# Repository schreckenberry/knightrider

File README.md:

# knightrider

project for university, blinking some ws2812b with a stm32f4/7

...git just because, nothing spectecular

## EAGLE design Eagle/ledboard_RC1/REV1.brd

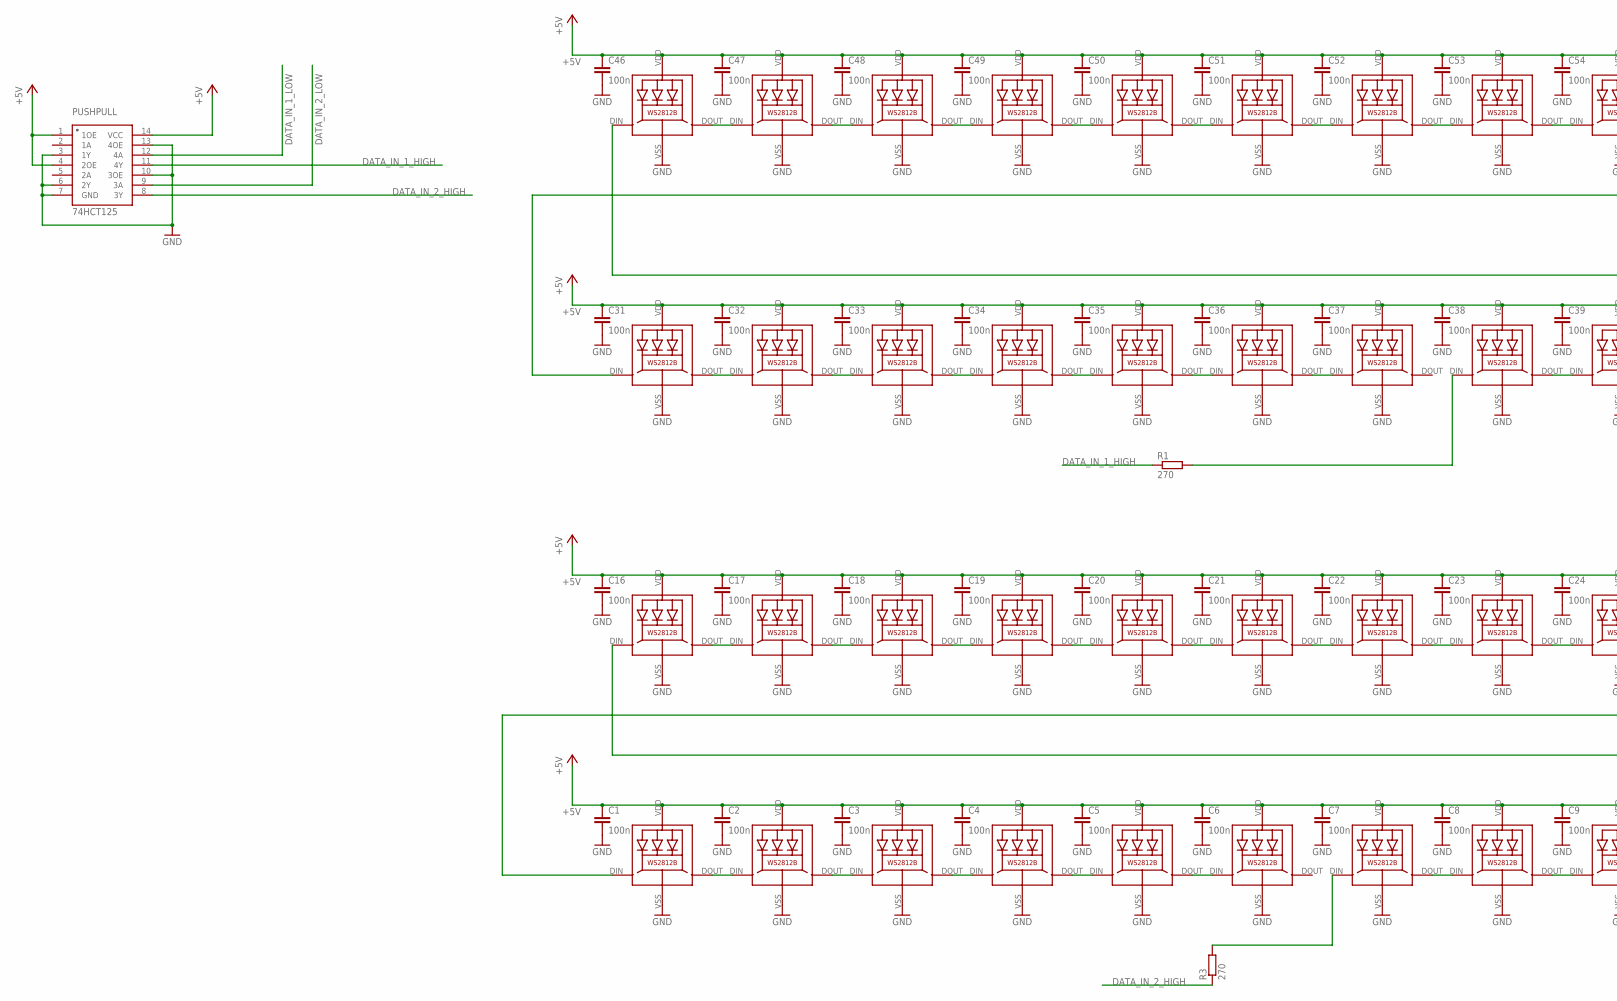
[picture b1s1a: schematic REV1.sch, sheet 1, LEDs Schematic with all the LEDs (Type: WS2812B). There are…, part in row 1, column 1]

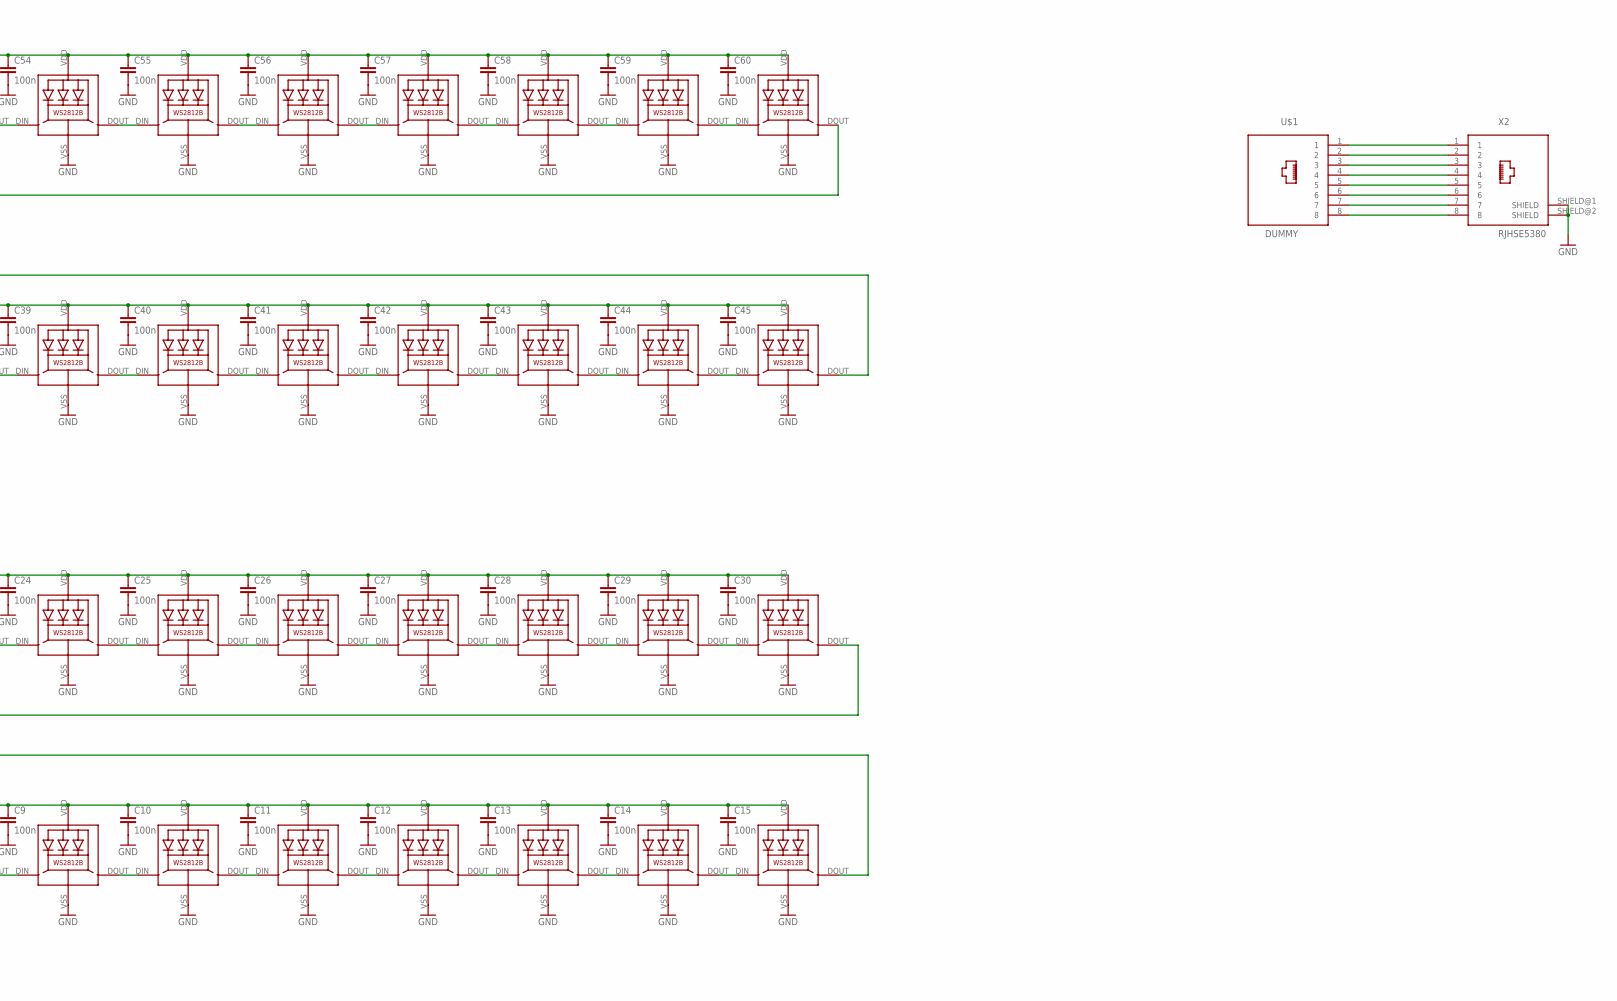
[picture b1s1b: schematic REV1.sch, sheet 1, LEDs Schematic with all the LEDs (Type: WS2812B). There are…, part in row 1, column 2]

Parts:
C1, C2, C3, C4, C5, C6, C7, C8, C9, C10, C11, C12, C13, C14, C15, C16, C17, C18, C19, C20, C21, C22, C23, C24, C25, C26, C27, C28, C29, C30, C31, C32, C33, C34, C35, C36, C37, C38, C39, C40, C41, C42, C43, C44, C45, C46, C47, C48, C49, C50, C51, C52, C53, C54, C55, C56, C57, C58, C59, C60: 100n; C0603
LED1, LED2, LED3, LED4, LED5, LED6, LED7, LED8, LED9, LED10, LED11, LED12, LED13, LED14, LED15, LED16, LED17, LED18, LED19, LED20, LED21, LED22, LED23, LED24, LED25, LED26, LED27, LED28, LED29, LED30, LED31, LED32, LED33, LED34, LED35, LED36, LED37, LED38, LED39, LED40, LED41, LED42, LED43, LED44, LED45, LED46, LED47, LED48, LED49, LED50, LED51, LED52, LED53, LED54, LED55, LED56, LED57, LED58, LED59, LED60: WS2812B
PUSHPULL: 74HCT125; SO-14DW
R1, R3: 270; R0603
U$1: DUMMY
X2: RJHSE5380

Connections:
+5V: C1.1, C2.1, C3.1, C4.1, C5.1, C6.1, C7.1, C8.1, C9.1, C10.1, C11.1, C12.1, C13.1, C14.1, C15.1, C16.1, C17.1, C18.1, C19.1, C20.1, C21.1, C22.1, C23.1, C24.1, C25.1, C26.1, C27.1, C28.1, C29.1, C30.1, C31.1, C32.1, C33.1, C34.1, C35.1, C36.1, C37.1, C38.1, C39.1, C40.1, C41.1, C42.1, C43.1, C44.1, C45.1, C46.1, C47.1, C48.1, C49.1, C50.1, C51.1, C52.1, C53.1, C54.1, C55.1, C56.1, C57.1, C58.1, C59.1, C60.1, LED1.VDD, LED2.VDD, LED3.VDD, LED4.VDD, LED5.VDD, LED6.VDD, LED7.VDD, LED8.VDD, LED9.VDD, LED10.VDD, LED11.VDD, LED12.VDD, LED13.VDD, LED14.VDD, LED15.VDD, LED16.VDD, LED17.VDD, LED18.VDD, LED19.VDD, LED20.VDD, LED21.VDD, LED22.VDD, LED23.VDD, LED24.VDD, LED25.VDD, LED26.VDD, LED27.VDD, LED28.VDD, LED29.VDD, LED30.VDD, LED31.VDD, LED32.VDD, LED33.VDD, LED34.VDD, LED35.VDD, LED36.VDD, LED37.VDD, LED38.VDD, LED39.VDD, LED40.VDD, LED41.VDD, LED42.VDD, LED43.VDD, LED44.VDD, LED45.VDD, LED46.VDD, LED47.VDD, LED48.VDD, LED49.VDD, LED50.VDD, LED51.VDD, LED52.VDD, LED53.VDD, LED54.VDD, LED55.VDD, LED56.VDD, LED57.VDD, LED58.VDD, LED59.VDD, LED60.VDD, PUSHPULL.1 (1OE), PUSHPULL.4 (2OE), PUSHPULL.14 (VCC); also elsewhere on the board
DATA_IN_1_HIGH: PUSHPULL.11 (4Y), R1.1
DATA_IN_1_LOW: PUSHPULL.12 (4A); also elsewhere on the board
DATA_IN_2_HIGH: PUSHPULL.8 (3Y), R3.1
DATA_IN_2_LOW: PUSHPULL.9 (3A); also elsewhere on the board
GND: C1.2, C2.2, C3.2, C4.2, C5.2, C6.2, C7.2, C8.2, C9.2, C10.2, C11.2, C12.2, C13.2, C14.2, C15.2, C16.2, C17.2, C18.2, C19.2, C20.2, C21.2, C22.2, C23.2, C24.2, C25.2, C26.2, C27.2, C28.2, C29.2, C30.2, C31.2, C32.2, C33.2, C34.2, C35.2, C36.2, C37.2, C38.2, C39.2, C40.2, C41.2, C42.2, C43.2, C44.2, C45.2, C46.2, C47.2, C48.2, C49.2, C50.2, C51.2, C52.2, C53.2, C54.2, C55.2, C56.2, C57.2, C58.2, C59.2, C60.2, LED1.VSS (GND), LED2.VSS (GND), LED3.VSS (GND), LED4.VSS (GND), LED5.VSS (GND), LED6.VSS (GND), LED7.VSS (GND), LED8.VSS (GND), LED9.VSS (GND), LED10.VSS (GND), LED11.VSS (GND), LED12.VSS (GND), LED13.VSS (GND), LED14.VSS (GND), LED15.VSS (GND), LED16.VSS (GND), LED17.VSS (GND), LED18.VSS (GND), LED19.VSS (GND), LED20.VSS (GND), LED21.VSS (GND), LED22.VSS (GND), LED23.VSS (GND), LED24.VSS (GND), LED25.VSS (GND), LED26.VSS (GND), LED27.VSS (GND), LED28.VSS (GND), LED29.VSS (GND), LED30.VSS (GND), LED31.VSS (GND), LED32.VSS (GND), LED33.VSS (GND), LED34.VSS (GND), LED35.VSS (GND), LED36.VSS (GND), LED37.VSS (GND), LED38.VSS (GND), LED39.VSS (GND), LED40.VSS (GND), LED41.VSS (GND), LED42.VSS (GND), LED43.VSS (GND), LED44.VSS (GND), LED45.VSS (GND), LED46.VSS (GND), LED47.VSS (GND), LED48.VSS (GND), LED49.VSS (GND), LED50.VSS (GND), LED51.VSS (GND), LED52.VSS (GND), LED53.VSS (GND), LED54.VSS (GND), LED55.VSS (GND), LED56.VSS (GND), LED57.VSS (GND), LED58.VSS (GND), LED59.VSS (GND), LED60.VSS (GND), PUSHPULL.3 (1Y), PUSHPULL.6 (2Y), PUSHPULL.7 (GND), PUSHPULL.10 (3OE), PUSHPULL.13 (4OE), X2.SHIELD@1 (SHIELD), X2.SHIELD@2 (SHIELD); also elsewhere on the board
unnamed: LED45.DOUT (DO), LED46.DIN (DI)
unnamed: LED46.DOUT (DO), LED47.DIN (DI)
unnamed: LED47.DOUT (DO), LED48.DIN (DI)
unnamed: LED48.DOUT (DO), LED49.DIN (DI)
unnamed: LED49.DOUT (DO), LED50.DIN (DI)
unnamed: LED50.DOUT (DO), LED51.DIN (DI)
unnamed: LED51.DOUT (DO), LED52.DIN (DI)
unnamed: LED52.DOUT (DO), LED53.DIN (DI)
unnamed: LED53.DOUT (DO), LED54.DIN (DI)
unnamed: LED54.DOUT (DO), LED55.DIN (DI)
unnamed: LED55.DOUT (DO), LED56.DIN (DI)
unnamed: LED56.DOUT (DO), LED57.DIN (DI)
unnamed: LED57.DOUT (DO), LED58.DIN (DI)
unnamed: LED58.DOUT (DO), LED59.DIN (DI)
unnamed: LED59.DOUT (DO), LED60.DIN (DI)
unnamed: LED31.DIN (DI), LED60.DOUT (DO)
unnamed: LED1.DIN (DI), LED30.DOUT (DO)
unnamed: LED1.DOUT (DO), LED2.DIN (DI)
unnamed: LED2.DOUT (DO), LED3.DIN (DI)
unnamed: LED3.DOUT (DO), LED4.DIN (DI)
unnamed: LED4.DOUT (DO), LED5.DIN (DI)
unnamed: LED7.DIN (DI), R3.2
unnamed: LED5.DOUT (DO), LED6.DIN (DI)
unnamed: LED7.DOUT (DO), LED8.DIN (DI)
unnamed: LED8.DOUT (DO), LED9.DIN (DI)
unnamed: LED9.DOUT (DO), LED10.DIN (DI)
unnamed: LED10.DOUT (DO), LED11.DIN (DI)
unnamed: LED11.DOUT (DO), LED12.DIN (DI)
unnamed: LED12.DOUT (DO), LED13.DIN (DI)
unnamed: LED13.DOUT (DO), LED14.DIN (DI)
unnamed: LED14.DOUT (DO), LED15.DIN (DI)
unnamed: LED15.DOUT (DO), LED16.DIN (DI)
unnamed: LED16.DOUT (DO), LED17.DIN (DI)
unnamed: LED17.DOUT (DO), LED18.DIN (DI)
unnamed: LED18.DOUT (DO), LED19.DIN (DI)
unnamed: LED19.DOUT (DO), LED20.DIN (DI)
unnamed: LED20.DOUT (DO), LED21.DIN (DI)
unnamed: LED21.DOUT (DO), LED22.DIN (DI)
unnamed: LED22.DOUT (DO), LED23.DIN (DI)
unnamed: LED23.DOUT (DO), LED24.DIN (DI)
unnamed: LED24.DOUT (DO), LED25.DIN (DI)
unnamed: LED25.DOUT (DO), LED26.DIN (DI)
unnamed: LED26.DOUT (DO), LED27.DIN (DI)
unnamed: LED27.DOUT (DO), LED28.DIN (DI)
unnamed: LED28.DOUT (DO), LED29.DIN (DI)
unnamed: LED29.DOUT (DO), LED30.DIN (DI)
unnamed: LED38.DIN (DI), R1.2
unnamed: LED31.DOUT (DO), LED32.DIN (DI)
unnamed: LED32.DOUT (DO), LED33.DIN (DI)
unnamed: LED33.DOUT (DO), LED34.DIN (DI)
unnamed: LED34.DOUT (DO), LED35.DIN (DI)
unnamed: LED35.DOUT (DO), LED36.DIN (DI)
unnamed: LED36.DOUT (DO), LED37.DIN (DI)
unnamed: U$1.1, X2.1
unnamed: LED38.DOUT (DO), LED39.DIN (DI)
unnamed: LED39.DOUT (DO), LED40.DIN (DI)
unnamed: LED40.DOUT (DO), LED41.DIN (DI)
unnamed: LED41.DOUT (DO), LED42.DIN (DI)
unnamed: LED42.DOUT (DO), LED43.DIN (DI)
unnamed: LED43.DOUT (DO), LED44.DIN (DI)
unnamed: LED44.DOUT (DO), LED45.DIN (DI)
unnamed: U$1.2, X2.2
unnamed: U$1.3, X2.3
unnamed: U$1.4, X2.4
unnamed: U$1.5, X2.5
unnamed: U$1.6, X2.6
unnamed: U$1.7, X2.7
unnamed: U$1.8, X2.8

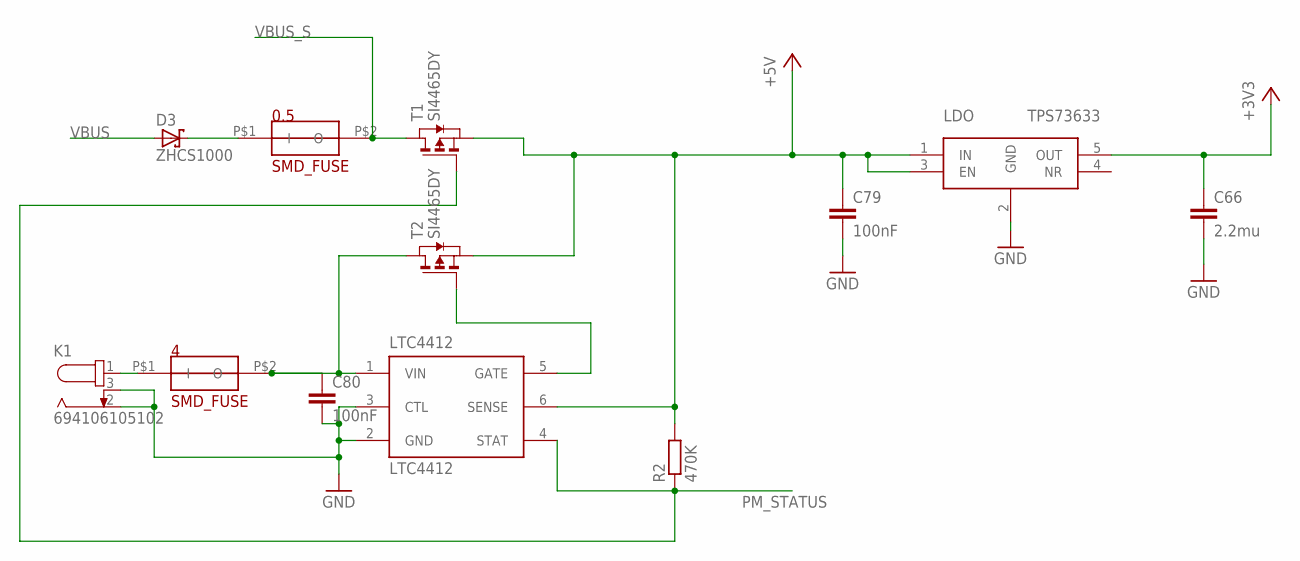
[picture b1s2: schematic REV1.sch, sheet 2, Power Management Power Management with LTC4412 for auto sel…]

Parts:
0.5, 4: SMD_FUSE; FUSE
C66: 2.2mu; C0603
C79, C80: 100nF; C0603
D3: ZHCS1000; SOT23
K1: 694106105102
LDO: TPS73633; SOT23-DBV
LTC4412: LTC4412; SOT23-6L
R2: 470K; R0603
T1, T2: SI4465DY; SO08

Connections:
+3V3: C66.1, LDO.5 (OUT); also elsewhere on the board
+5V: C79.1, LDO.1 (IN), LDO.3 (EN), LTC4412.6 (SENSE), R2.2, T1.1 (S), T1.2 (S), T1.3 (S), T2.1 (S), T2.2 (S), T2.3 (S); also elsewhere on the board
GND: C66.2, C79.2, C80.2, K1.2, K1.3, LDO.2 (GND), LTC4412.2 (GND), LTC4412.3 (CTL); also elsewhere on the board
unnamed: LTC4412.5 (GATE), T2.4 (G)
unnamed: 0.5.P$1 (I), D3.1 (C)
PM_STATUS: LTC4412.4 (STAT), R2.1, T1.4 (G); also elsewhere on the board
VBUS: D3.3 (A); also elsewhere on the board
VBUS_S: 0.5.P$2 (O), T1.5 (D), T1.6 (D), T1.7 (D), T1.8 (D); also elsewhere on the board
V_5: 4.P$2 (O), C80.1, LTC4412.1 (VIN), T2.5 (D), T2.6 (D), T2.7 (D), T2.8 (D)
V_IN: 4.P$1 (I), K1.1

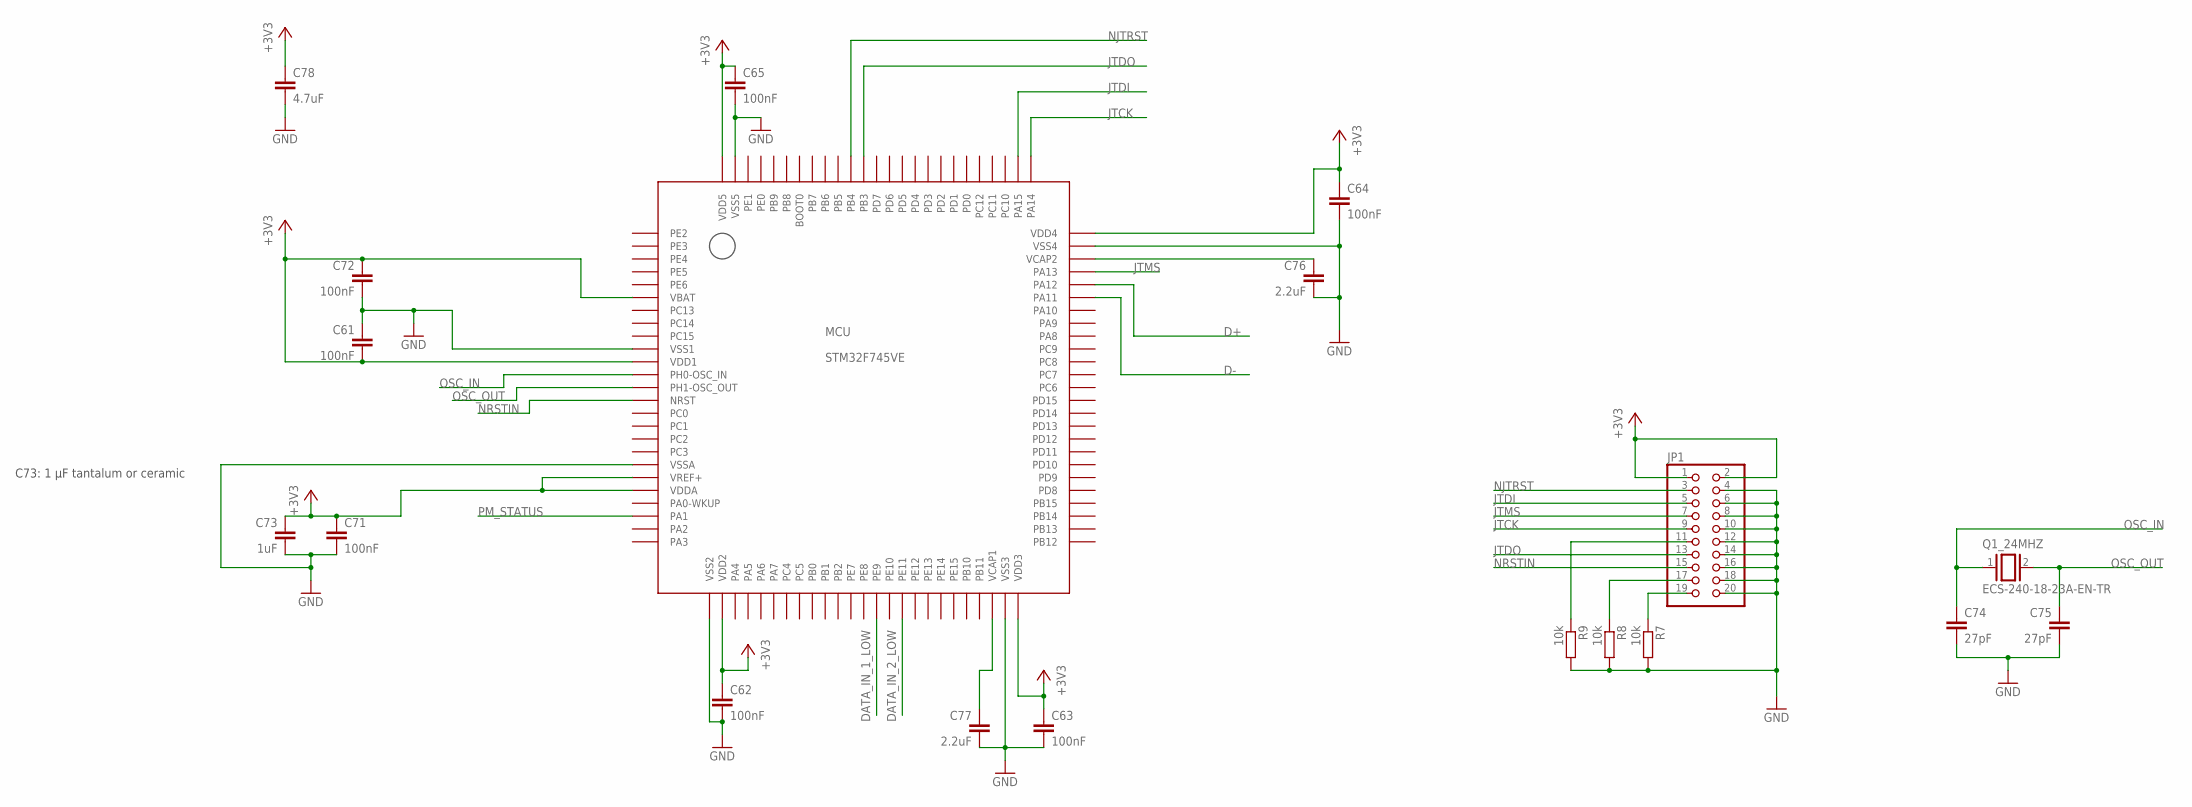
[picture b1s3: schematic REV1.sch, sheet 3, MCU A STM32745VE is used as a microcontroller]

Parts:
C61, C62, C63, C64, C65, C71, C72: 100nF; C0603
C73: 1uF; C0603
C74, C75: 27pF; C0603
C76, C77: 2.2uF; C0603
C78: 4.7uF; C0603
JP1: PINHD-2X10_2.54-SMD; 2X10SMD
MCU: STM32F745VE; LQFP100
Q1_24MHZ: ECS-240-18-23A-EN-TR; ESC64A
R7, R8, R9: 10k; R0603

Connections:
+3V3: C61.2, C62.1, C63.1, C64.1, C65.1, C71.1, C72.1, C73.1, C78.1, JP1.1, JP1.2, MCU.6 (VBAT), MCU.11 (VDD1), MCU.20 (VREF+), MCU.21 (VDDA), MCU.27 (VDD2), MCU.50 (VDD3), MCU.75 (VDD4), MCU.100 (VDD5); also elsewhere on the board
D+: MCU.71 (PA12); also elsewhere on the board
D-: MCU.70 (PA11); also elsewhere on the board
DATA_IN_1_LOW: MCU.39 (PE9); also elsewhere on the board
DATA_IN_2_LOW: MCU.41 (PE11); also elsewhere on the board
GND: C61.1, C62.2, C63.2, C64.2, C65.2, C71.2, C72.2, C73.2, C74.2, C75.2, C76.2, C77.2, C78.2, JP1.4, JP1.6, JP1.8, JP1.10, JP1.12, JP1.14, JP1.16, JP1.18, JP1.20, MCU.10 (VSS1), MCU.19 (VSSA), MCU.26 (VSS2), MCU.49 (VSS3), MCU.74 (VSS4), MCU.99 (VSS5), R7.2, R8.2, R9.2; also elsewhere on the board
JTCK: JP1.9, MCU.76 (PA14)
JTDI: JP1.5, MCU.77 (PA15)
JTDO: JP1.13, MCU.89 (PB3)
JTMS: JP1.7, MCU.72 (PA13)
unnamed: C77.1, MCU.48 (VCAP1)
unnamed: C76.1, MCU.73 (VCAP2)
unnamed: JP1.19, R7.1
unnamed: JP1.17, R8.1
unnamed: JP1.11, R9.1
NJTRST: JP1.3, MCU.90 (PB4)
NRSTIN: JP1.15, MCU.14 (NRST)
OSC_IN: C74.1, MCU.12 (PH0-OSC_IN), Q1_24MHZ.1
OSC_OUT: C75.1, MCU.13 (PH1-OSC_OUT), Q1_24MHZ.2
PM_STATUS: MCU.23 (PA1); also elsewhere on the board

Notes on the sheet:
C73: 1 μF tantalum or ceramic

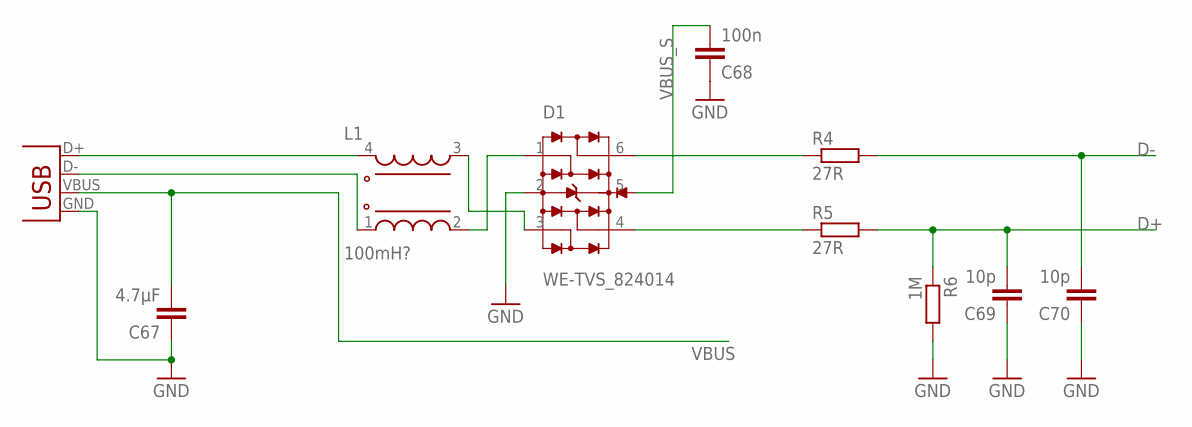
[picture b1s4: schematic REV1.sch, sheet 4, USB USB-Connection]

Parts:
C67: 4.7µF; C0603
C68: 100n; C0603
C69, C70: 10p; C0603
D1: WE-TVS_824014; WE-TVS_SOT23-6L
L1: 100mH?; WE-CNSW_0805
R4, R5: 27R; R0603
R6: 1M; R0603
X1: USBSMD; USB-MINIB

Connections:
D+: C69.2, R5.2, R6.1; also elsewhere on the board
D+_TMP: L1.4 (1), X1.D+
D-: C70.2, R4.2; also elsewhere on the board
D-_TMP: L1.1 (4), X1.D-
GND: C67.1, C68.1, C69.1, C70.1, D1.2 (GND), R6.2, X1.GND; also elsewhere on the board
unnamed: D1.1, L1.2 (3)
unnamed: D1.3 (2), L1.3 (2)
unnamed: D1.6 (4), R4.1
unnamed: D1.4 (3), R5.1
VBUS: C67.2, X1.VBUS; also elsewhere on the board
VBUS_S: C68.2, D1.5 (VDD); also elsewhere on the board

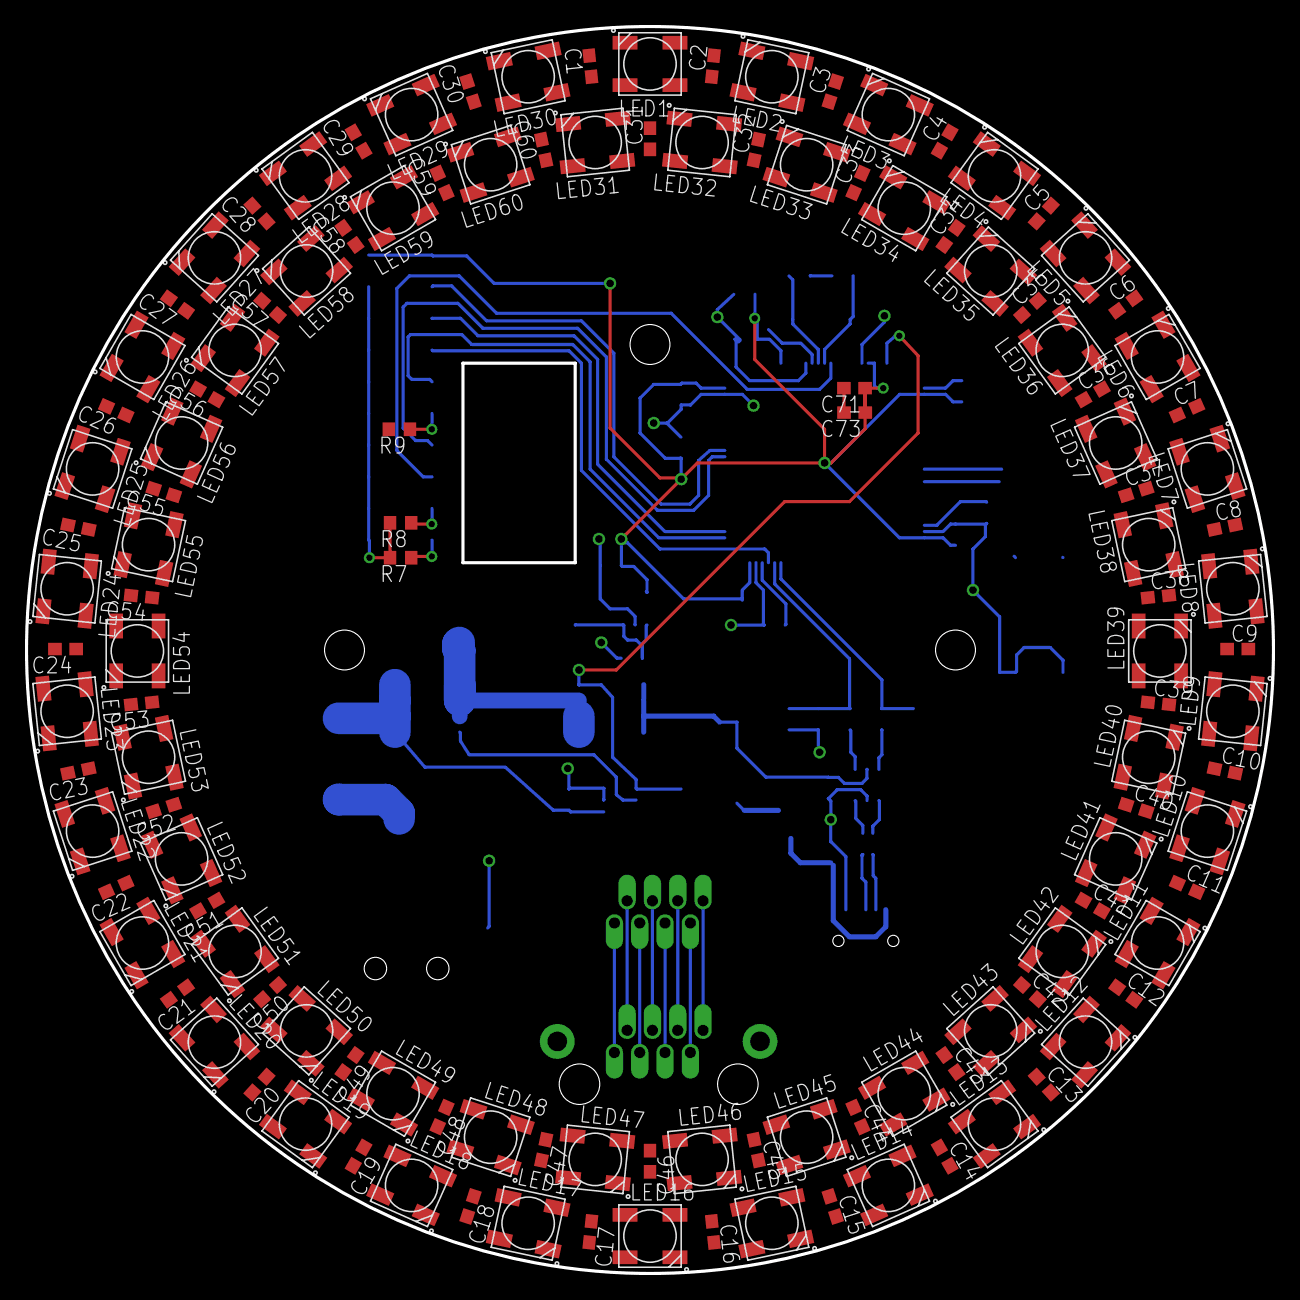
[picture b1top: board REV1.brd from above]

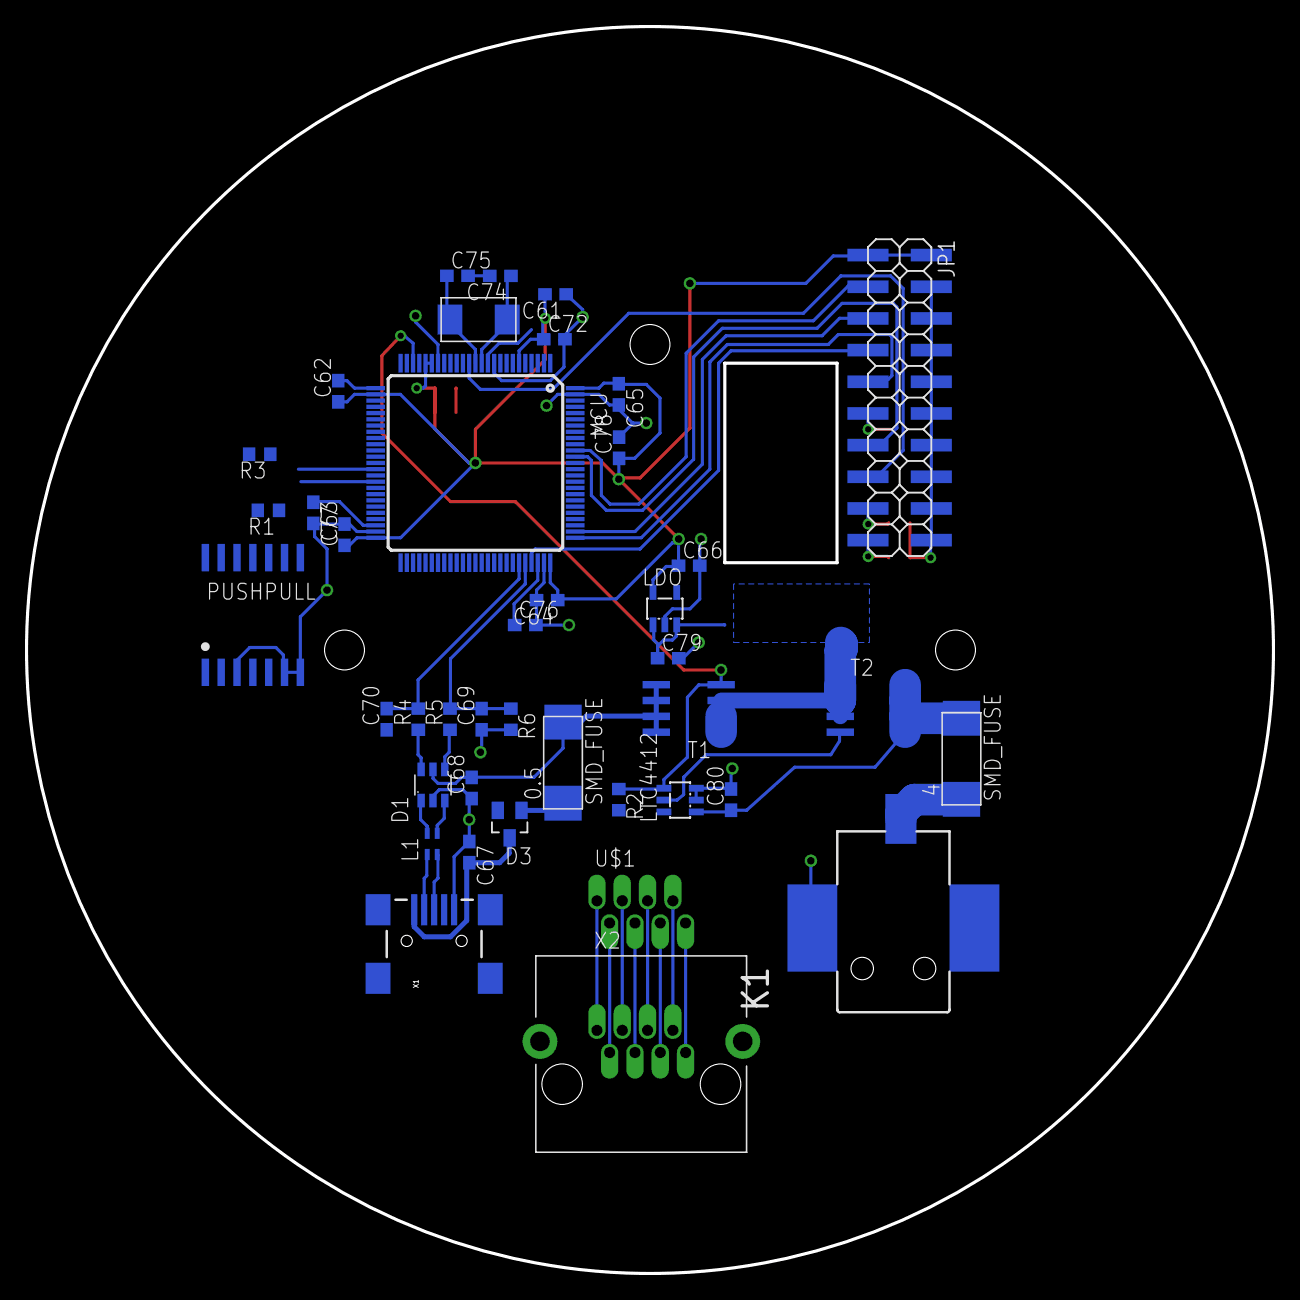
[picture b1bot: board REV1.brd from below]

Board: 2 copper layers, 100.0 x 100.0 mm, 166 parts (41 on the bottom side), 103 nets.

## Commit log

2016-05-11 first board ideas
2016-05-11 first ideas of board, some data sheets, firt schematic test
2016-05-11 wohoo
2016-05-12 new eagle libs, ws2812b and stm32f4 lqpf100 package
2016-05-12 circular layout script added
2016-05-12 blub
2016-05-12 board pic added
2016-05-14 LTSpice Files added
2016-05-24 updated eagle
2016-05-24 a lot of updates
2016-05-27 updated board
2016-05-27 First layout done, few changes for easier routing
2016-05-27 added pinhead lib
2016-05-31 new folder...
2016-05-31 forgotten board
2016-05-31 updated board layout

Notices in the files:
parts and their libraries:
Wurth_Elektronik_EMC_COMPONENTS_rev16c: Copyright: Würth Elektronik
